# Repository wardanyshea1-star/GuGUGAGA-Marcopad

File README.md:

# GUGUGAGA

Gugugaga pad is a 9 key macropad with a rotary encoder, an OLED Display. It uses kmk firmware.
It’s mainly designed for playing games.

## Features:
- 3d printed case
- 1x 0.91 inch OLED Display
- EC11 Rotary encoder
- 9 Keys

## CAD Model:
Everything fits together using extended bits on the bottom piece that fit into the above piece, and  2 screws.

## PCB
This is my pcb, made in KiCad.
- schematic

- pcb

- pcb in 3d viewer

## Firmware Overview
This hackpad uses KMK firmware for everything.
the rotary encoder changes volume. press to pause
The 9 keys are for moving up down sideways, space and mouse functions left click ad right click. and 2 other switches for copy and paste just because its convenient. Also the oled display shows the time( for not to keep playing for too long)

# BOM
Here should be everything you need to make this hackpad

- 9x MX-style Switches
- 9x DSA Keycaps
- 2x M3x16mm screws
- 2x M3x5mx4mm heatset inserts
- 9x 1N4148 Diodes.
1x 0.91" 128x32 OLED Display
1x EC11 Rotary Encoder
1x Seeed XIAO RP2040
2 printed parts

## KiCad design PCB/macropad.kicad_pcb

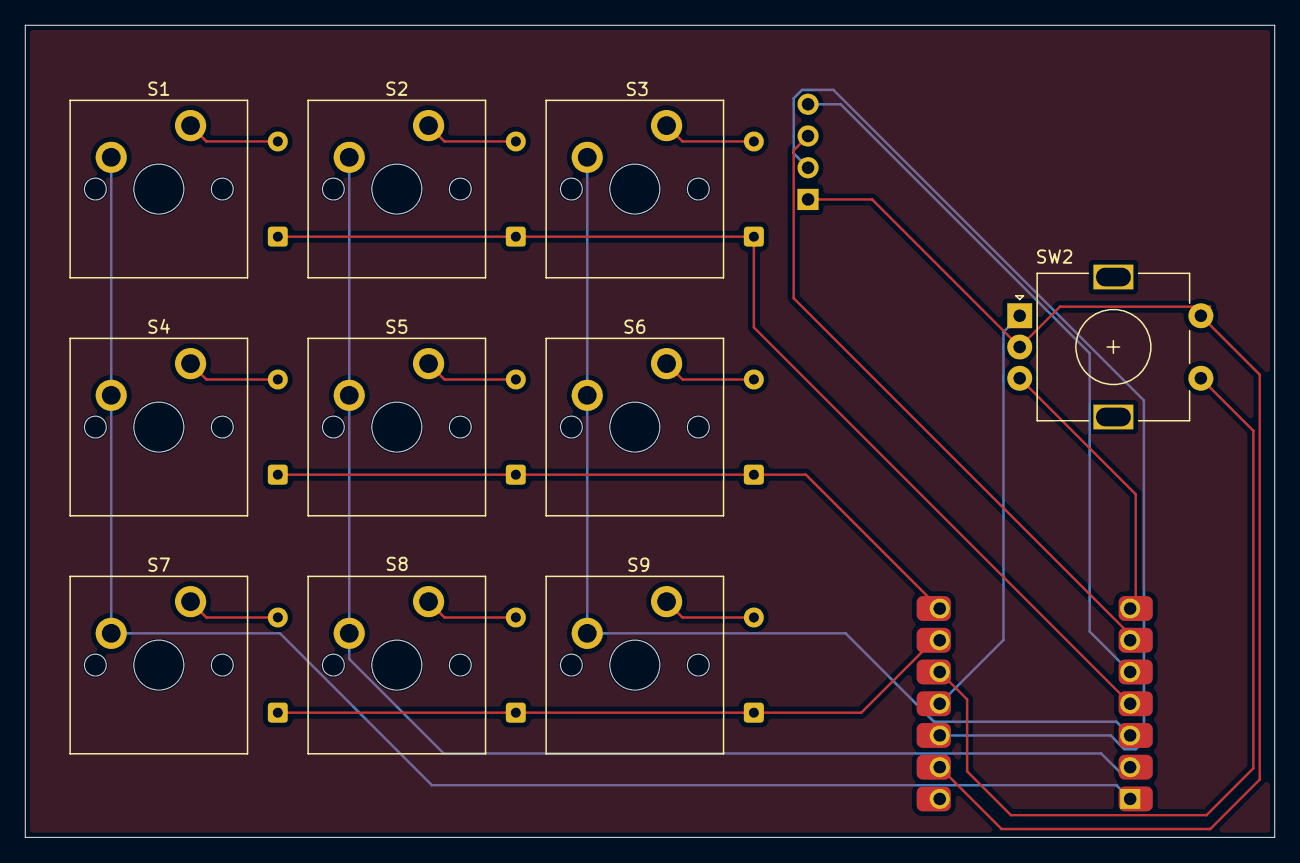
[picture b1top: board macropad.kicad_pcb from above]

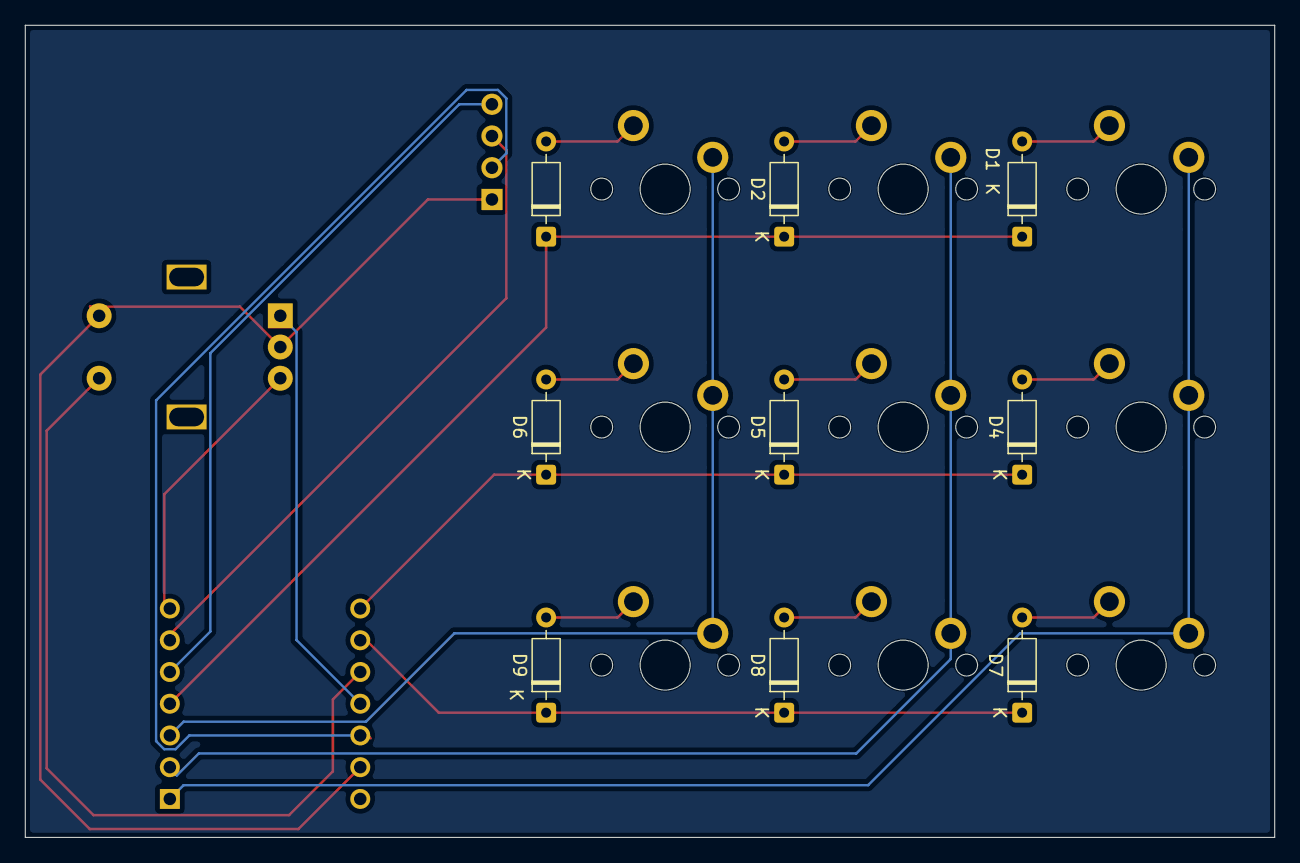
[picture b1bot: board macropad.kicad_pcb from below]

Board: 2 copper layers, 100.0 x 65.0 mm, 21 parts (9 on the bottom side), 22 nets.

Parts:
D1, D2, D3, D4, D5, D6, D7, D8, D9: 1N4148; D_DO-35_SOD27_P7.62mm_Horizontal
S1, S2, S3, S4, S5, S6, S7, S8, S9: MX_PCB_1.00u
SW2: RotaryEncoder_Switch; RotaryEncoder_Alps_EC11E-Switch_Vertical_H20mm
U1: MCU_Seeed_XIAO_RP2040; Seeed_XIAO_RP2040
U2: ER_OLEDM0.91_1x-I2C; OLED_128x32

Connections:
unnamed: D1.2 (A), S1.2
unnamed: D2.2 (A), S2.2
unnamed: D3.2 (A), S3.2
unnamed: D4.2 (A), S4.2
unnamed: D5.2 (A), S5.2
unnamed: D6.2 (A), S6.2
unnamed: D7.2 (A), S7.2
unnamed: D8.2 (A), S8.2
unnamed: D9.2 (A), S9.2
column 0: S1.1, S4.1, S7.1, U1.1 (PA02_A0_D0)
column 1: S2.1, S5.1, S8.1, U1.2 (PA4_A1_D1)
column 2: S3.1, S6.1, S9.1, U1.3 (PA10_A2_D2)
gnd: SW2.C, SW2.S2, U1.13 (GND), U2.1 (GND)
miso: SW2.S1, U1.10 (PA5_A9_D9_MISO)
mosi: SW2.A, U1.11 (PA6_A10_D10_MOSI)
row 0: D1.1 (K), D2.1 (K), D3.1 (K), U1.4 (PA11_A3_D3)
row 1: D4.1 (K), D5.1 (K), D6.1 (K), U1.8 (PB09_A7_D7_RX)
row 2: D7.1 (K), D8.1 (K), D9.1 (K), U1.9 (PA7_A8_D8_SCK)
scl: U1.6 (PA9_A5_D5_SCL), U2.3 (SCL)
sda: U1.5 (PA8_A4_D4_SDA), U2.4 (SDA)
tx: SW2.B, U1.7 (PB08_A6_D6_TX)
vcc: U1.12 (3V3), U2.2 (VCC)
